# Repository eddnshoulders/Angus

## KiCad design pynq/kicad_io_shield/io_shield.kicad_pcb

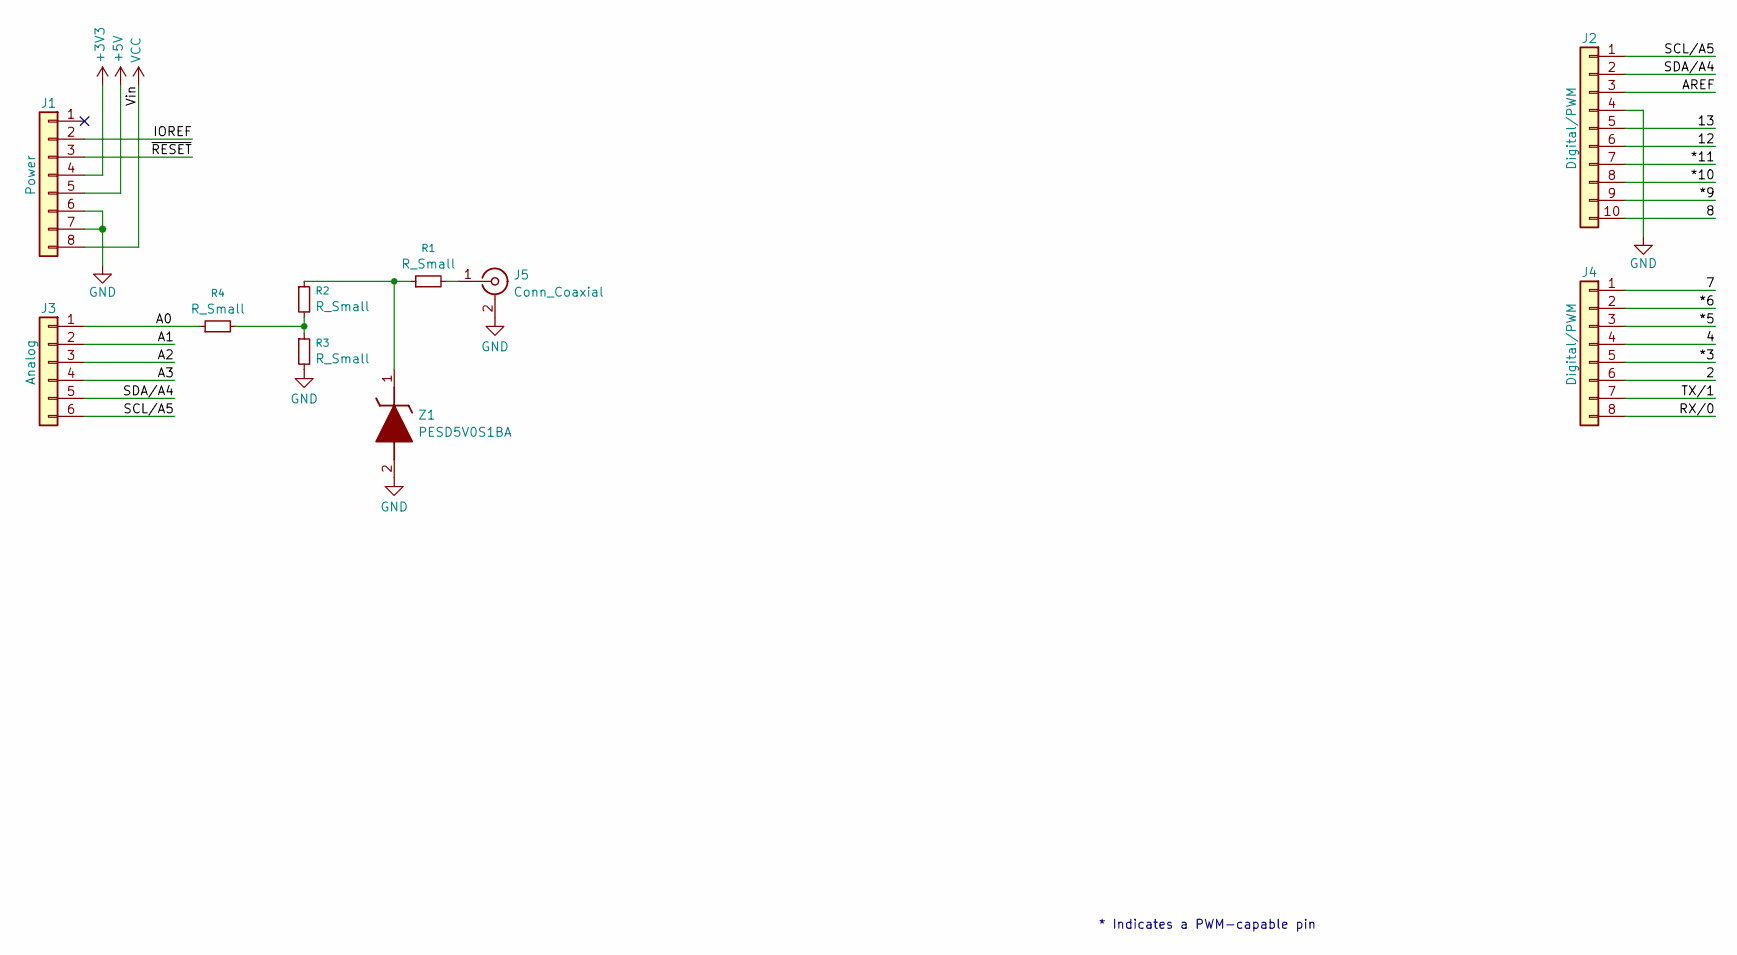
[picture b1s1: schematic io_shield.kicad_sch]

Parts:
J1: Power; PinSocket_1x08_P2.54mm_Vertical
J2: Digital/PWM; PinSocket_1x10_P2.54mm_Vertical
J3: Analog; PinSocket_1x06_P2.54mm_Vertical
J4: Digital/PWM; PinSocket_1x08_P2.54mm_Vertical
J5: Conn_Coaxial; SMB_Jack_Vertical
R1, R2, R3, R4: R_Small; R_0805_2012Metric_Pad1.20x1.40mm_HandSolder
Z1: PESD5V0S1BA; SOD2512X110N; Manufacturer_Part_Number PESD5V0S1BA; Mouser Part Number N/A

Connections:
+3V3: J1.4
+5V: J1.5
/2: J4.6
/4: J4.4
/7: J4.1
/8: J2.10
/12: J2.6
/13: J2.5
/*3: J4.5
/*5: J4.3
/*6: J4.2
/*9: J2.9
/*10: J2.8
/*11: J2.7
/A0: J3.1, R4.1
/A1: J3.2
/A2: J3.3
/A3: J3.4
/AREF: J2.3
/IOREF: J1.2
/RX/0: J4.8
/SCL/A5: J2.1, J3.6
/SDA/A4: J2.2, J3.5
/TX/1: J4.7
/~RESET: J1.3
GND: J1.6, J1.7, J2.4, J5.2 (Ext), R3.2, Z1.2 (A)
unnamed: J5.1 (In), R1.2
unnamed: R2.2, R3.1, R4.2
unnamed: R1.1, R2.1, Z1.1 (K)
VCC: J1.8

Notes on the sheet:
* Indicates a PWM-capable pin

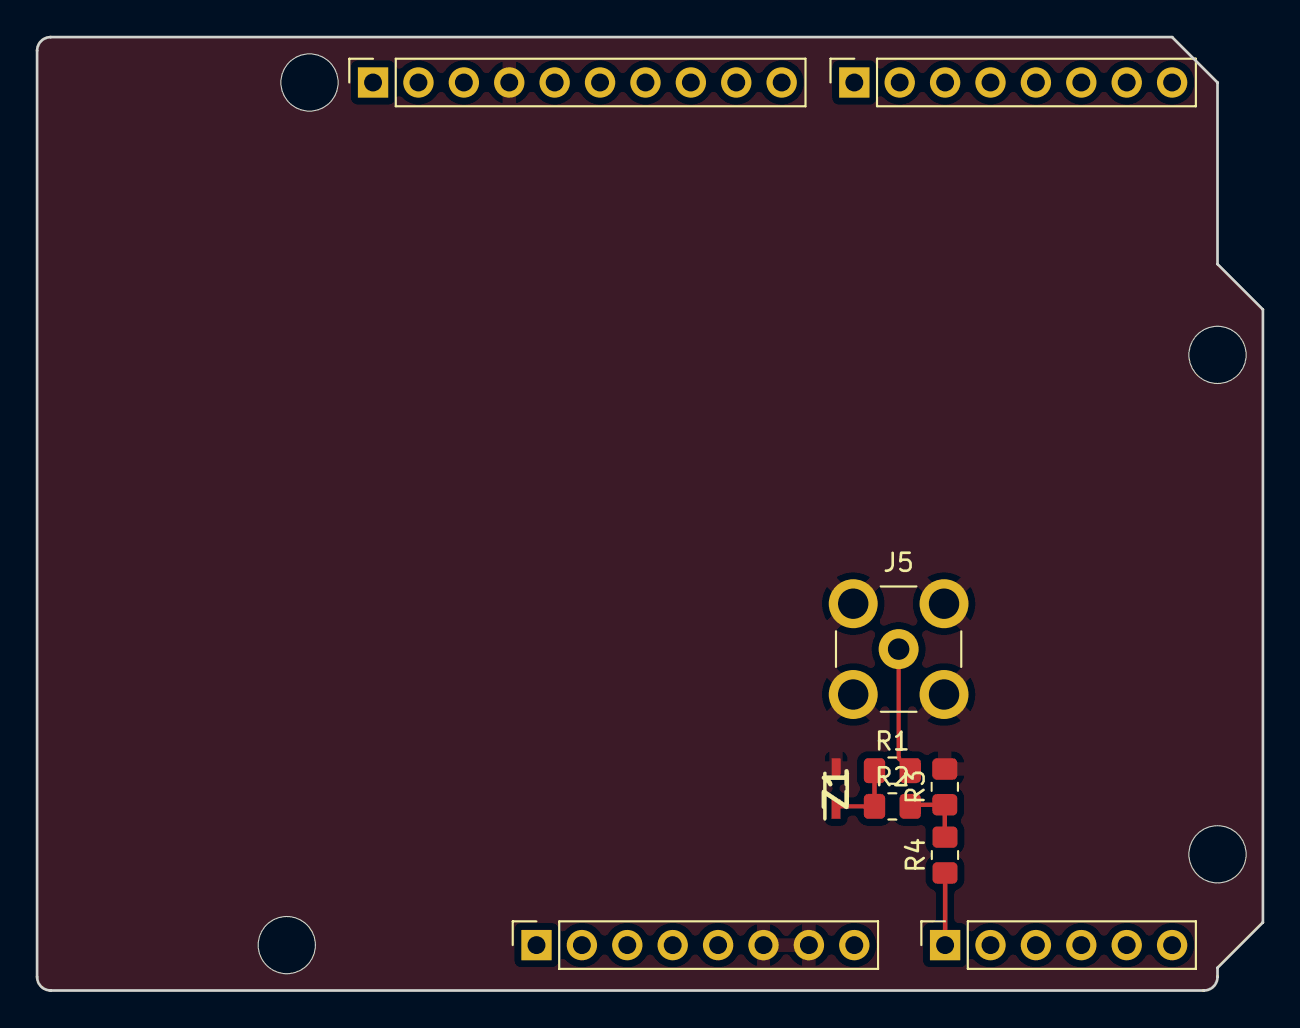
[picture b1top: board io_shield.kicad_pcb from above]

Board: 2 copper layers, 68.6 x 53.3 mm, 14 parts (0 on the bottom side), 7 nets.

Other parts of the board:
MH1, MH2, MH3, MH4: MountingHole_3.2mm

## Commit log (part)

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2026-05-24 Initial commit - 1st hardware tested version. Needs physical outputs and axi registers for sync debugging.
2026-05-24 Add debug outputs to angle_engine: div_valid, synced, nco_inc, phase_error, correction
    These five internal signals are exposed as output ports to allow AXI register
    readback for diagnosing PLL behaviour:
    - div_valid_out: confirms the sequential divider has produced a valid result
    - synced_out: shows whether the NCO sync gate is open
    - nco_inc_out: the current NCO frequency word (proportional to tooth period)
    - phase_error_out: signed phase error fed into the PI loop filter
2026-05-25 Changes to remove "PYNQ-Z2 v1.0.xdc" from angus.xpr and also move digital_out_0[4] and digital_out_0[5] pin asssignments to avoid MRCC and SRCC pins conflicting with XADC placement.
    Still getting placement errors during implementation.
2026-05-26 Add configurable debug pulse stretcher to sample_trigger
    sample_pulse output on the Pi header debug pin was one clock cycle
    (10ns) - too short to trigger reliably on a scope.
    Changes:
    - sample_trigger now outputs two signals:
    sample_pulse - one-cycle functional trigger (sample_packer, xadc)
    sample_pulse_dbg - stretched version for scope/LA debug output
2026-05-26 Fix phase fault handling: increment sync_loss, add phase_fault_drop control
    Two fixes to sync.vhd:
    1. Phase fault now increments sync_loss_count
    Previously a cam edge arriving outside the tolerance window only set
    phase_flt and incremented phase_fault_count. sync_loss_count was not
    incremented so the fault was invisible to the monitoring tool.
    sync_loss_count now increments on every phase fault event.
2026-05-27 Add CONFIG_APPLY mechanism for atomic startup configuration
    Separates registers into two categories:
    Startup config (latched atomically on CONFIG_APPLY pulse):
    edge_select, ang_sel, ref_sel, gap_threshold, n_teeth, n_missing
    These affect signal integrity if changed while running.
    Write all values first, then pulse CONTROL[6]=1 to apply.
    Design remains in reset (config_valid=0) until first CONFIG_APPLY.
2026-05-27 Rewire top.vhd for new architecture, update axi_lite_regs ports
    top.vhd - full rewire to new signal flow:
    New blocks instantiated:
    u_enc_input (stub)
    u_ang_sel (crank/encoder mux)
    u_cam_input (cam edge detector)
    u_peak_detector (stub)
2026-05-27 crank_input: rename edge_select->crank_edge_sel, add ppr_crank output
2026-05-27 angle_calc: replace degrees_per_edge division with case statement
    Avoids VHDL division operator width mismatch. Covers common ppr values:
    36, 58, 60, 72, 90, 120 teeth.
2026-05-27 axi_lite_regs: add count_fault read register at 0x6C
2026-05-27 top: rename crank_ab->ab_crank, crank_z->z_crank to match system diagram
2026-05-27 top: add a_raw/b_raw/z_raw encoder ports, stub to '0' pending encoder integration
2026-05-29 tb: add axi_lite_regs_tb (T1-T8: write/read, config_apply, rst, divider, fault_clear, status)
2026-05-29 src_sel: crank/encoder mux, all tests pass
2026-05-29 cam: edge detection + tooth count, T1-T4 pass
2026-05-29 speed: slow (z_period) and fast (ab_period) RPM, T1-T2 pass
2026-05-29 pll: NCO + PI loop, 0-7199 output, T1-T5 pass
2026-05-29 enc_tb: T1-T5 passing
2026-05-29 angus_regs: v2 register map, AngusRegs class, config_apply, status helpers
2026-05-29 axi_lite_regs_tb: update addresses for new register map, T1-T8 passing
2026-05-29 crank_tb: add crank_gap_period to port map and T5 test, T1-T5 passing
2026-05-29 phase: rename phase_ang_eng -> phase_eng_ang throughout
2026-05-29 top: wire angle_nco_clk_inc to pll, fix phase_eng_ang port names, remove TODOs
2026-05-29 top: wire fault src_sel/ref_sel/ab_count/ppr_conf/max_rpm, remove fault TODO
2026-05-29 top: reduce debug_out to 14 bits (bits 0-13 only, all assigned in XDC)
2026-05-30 angle_tb: add extra clock waits for registered angle_deg output, T1-T6 passing
2026-05-31 top: wire ref_angle from phase.vhd to axi_lite_regs REF_ANGLE register
    Was incorrectly wired to phase_ang_corr (continuously updated).
    Now correctly shows angle at last ref_edge detection.
2026-05-31 crank_tb: update port map and timing for archive-based implementation
2026-06-01 Updates to design docs. Added vivado/scripts/reset_and_synth.tcl. Added multicycle path constraints to angus.xdc
2026-06-03 Saving some small changes to tests before moving to v3 arch.
2026-06-04 ang_sel, tdc, trig, pack v3: angfac domain throughout
    ang_sel.vhd v3:
    Ports renamed: angle_deg_in->angle_angfac, pll_ang_hires->pll_angfac,
    ang_deg->ang_angfac. All signals 32-bit unsigned (was 16-bit degree).
    Pure combinatorial mux, no other changes.
    tdc.vhd v3 (new block):
    Converts {phase_eng, ang_angfac} (33-bit engine position) to
2026-06-04 angus.py: startup_conf()/runtime_conf() split, phase_ref_deg clean up
    - configure()/apply() replaced by startup_conf() and runtime_conf()
    - startup_conf(): all parameters requiring a hardware reset. Applies
    immediately on each call -- no separate apply() needed. Internal
    _apply_startup() writes all startup registers then toggles config_apply,
    followed immediately by _apply_runtime() so runtime values survive the reset.
    - runtime_conf(): all parameters that can change during operation without
2026-06-04 angus.py: move angfac conversions into Angus class
    _to_angfac() and _from_angfac() moved from module level into Angus as
    static methods and renamed:
    deg2angfac(deg) -- public, converts crank degrees to 32-bit angfac
    _angfac2deg(v) -- private, converts angfac to crank degrees
    Both callable through the instance (a.deg2angfac(), a._angfac2deg())
    or directly on the class. All internal callers updated.
2026-06-05 angle, fault, top: add ILA debug outputs
    angle.vhd:
    - angle_nco_clk_inc_valid added as output port (exposes clk_inc_valid).
    Goes low briefly each ab_edge while tooth divider runs (~32 clocks),
    stays high during interpolation. Key signal for verifying z_edge gap fix.
    fault.vhd:
    - Individual instantaneous fault flag outputs added:
2026-06-06 xadc_buffer.vhd, top.vhd: integrate XADC into v3
    xadc_buffer.vhd: ported from archive (CRLF stripped). No logic changes.
    - Event-mode XADC triggered by sample_pulse (= trig_pulse)
    - Latches all channels simultaneously on eos
    - 6-channel instantiation (VAUX1-VAUX6 -> pack adc_ch1-6)
    top.vhd:
    - Remove adc_ch1-6 as top-level input ports (now internal)
2026-06-07 xadc_buffer.vhd, xadc_buffer_tb.vhd: fix eoc/ch_valid timing and latch bug
    Three bugs found and fixed by testbench (4 tests all passing):
    Bug 1 -- eoc/ch_valid timing:
    p_ch_decode registers xadc_channel (1 clock delay). xadc_eoc is a
    1-clock pulse. Without registering eoc, ch_valid arrives 1 clock
    AFTER eoc so the FSM condition 'eoc=1 and ch_valid=1' was never true.
    Fix: register xadc_eoc in p_ch_decode as xadc_eoc_d; use in FSM.
2026-06-08 pack_tb.vhd: update for 3-word packet format with adc_ch0
    - Remove adc1-6 signals, add adc0 (512 = 0.125V test value)
    - N_WORDS: 6->3
    - Add T4: Word 2 content check (DI=0xA5, adc_ch0=512, lower 12 bits=0)
    - Update T5 pkt_count expectation: 3 packets not 2
    - All 8 tests passing
2026-06-10 Adding tests/pcyl_curves.
    Adding vivado/scripts/regen_ip.tcl
    Adding clean_cached bash script to remove all cached vivado files ready for full clean rebuild
2026-06-12 avg.vhd: fix registered output pipeline timing
    out_data is a registered signal so data must be pre-loaded one state
    before it needs to appear on m_axis_tdata. Pre-load chain:
    - OUT_IDLE: load rpm directly (lat_rpm also registered, not yet valid)
    - OUT_HDR0 on tready: pre-load lat_n for HDR1
    - OUT_HDR1 on tready: issue BRAM read for first bin
2026-06-12 avg_tb: fix T3 header sampling - wait until tvalid then sample immediately
    The two-step (wait for tvalid, wait for next rising edge) pattern was
    still catching HDR1 because the next rising edge after tvalid fires
    is already HDR1. Instead, sample immediately after wait until tvalid='1'
    with just wait for 1ns - data is stable within the HDR0 clock cycle.
    HDR1 data (lat_n) is then sampled on the following rising edge.
2026-06-12 avg: all 8 tests passing
    Key fixes in avg.vhd:
    - swap_ack: set when OUT_IDLE sees bank_full, held until bank_full
    clears (acc FSM processes it). Prevents one-cycle pulse miss and
    prevents CLR from zeroing wrong bank.
    - Pipelined BRAM reads: tvalid continuously high during streaming
    (one bin per clock, no RDREQ/RDWAIT gaps)
2026-06-14 avg: remove header words, fix bank swap race, fix tready routing
    avg.vhd:
    - Remove HDR0/HDR1 output states -- rpm and N available via AXI-Lite
    registers, no need to embed in stream
    - Output frame is now exactly 7200 words (bins 0..7199), matching
    bypass frame size at dma_buffer_size=1
    - Remove rpm port (no longer used)
2026-06-18 avg: add diagnostic counters and output FSM state for DMA1 debug
    New AXI-Lite read-only registers (avg<->DMA1 handshake visibility):
    0x114 AVG_IN_BEAT_COUNT -- s_axis beats accepted (bypass or accumulate)
    0x118 AVG_OUT_BEAT_COUNT -- m_axis beats accepted (tvalid & tready)
    0x11C AVG_OUT_TLAST_COUNT -- m_axis tlast beats accepted
    0x120 AVG_OUT_STALL_COUNT -- cycles tvalid=1, tready=0 (downstream stall)
    0x124 AVG_BAD_TLAST_COUNT -- tlast asserted on word 0 (framing bug check)
2026-06-19 Replacing avg module after extensive unsuccessful debugging on an excessively complicated version.
2026-06-22 raw DMA0 path: FIFO protection, software reset, dropped-packet counter
    Implements the raw DMA0 logging path hardening described in the spec:
    pack.vhd:
    - New port: raw_fifo_almost_full (in std_logic) -- asserted by the
    AXI Stream FIFO in the BD when it is nearly full.
    - New port: dropped_pkt_count (out unsigned(31 downto 0)).
    - New state: DROP. When a new packet would start (IDLE->WORD0) and
